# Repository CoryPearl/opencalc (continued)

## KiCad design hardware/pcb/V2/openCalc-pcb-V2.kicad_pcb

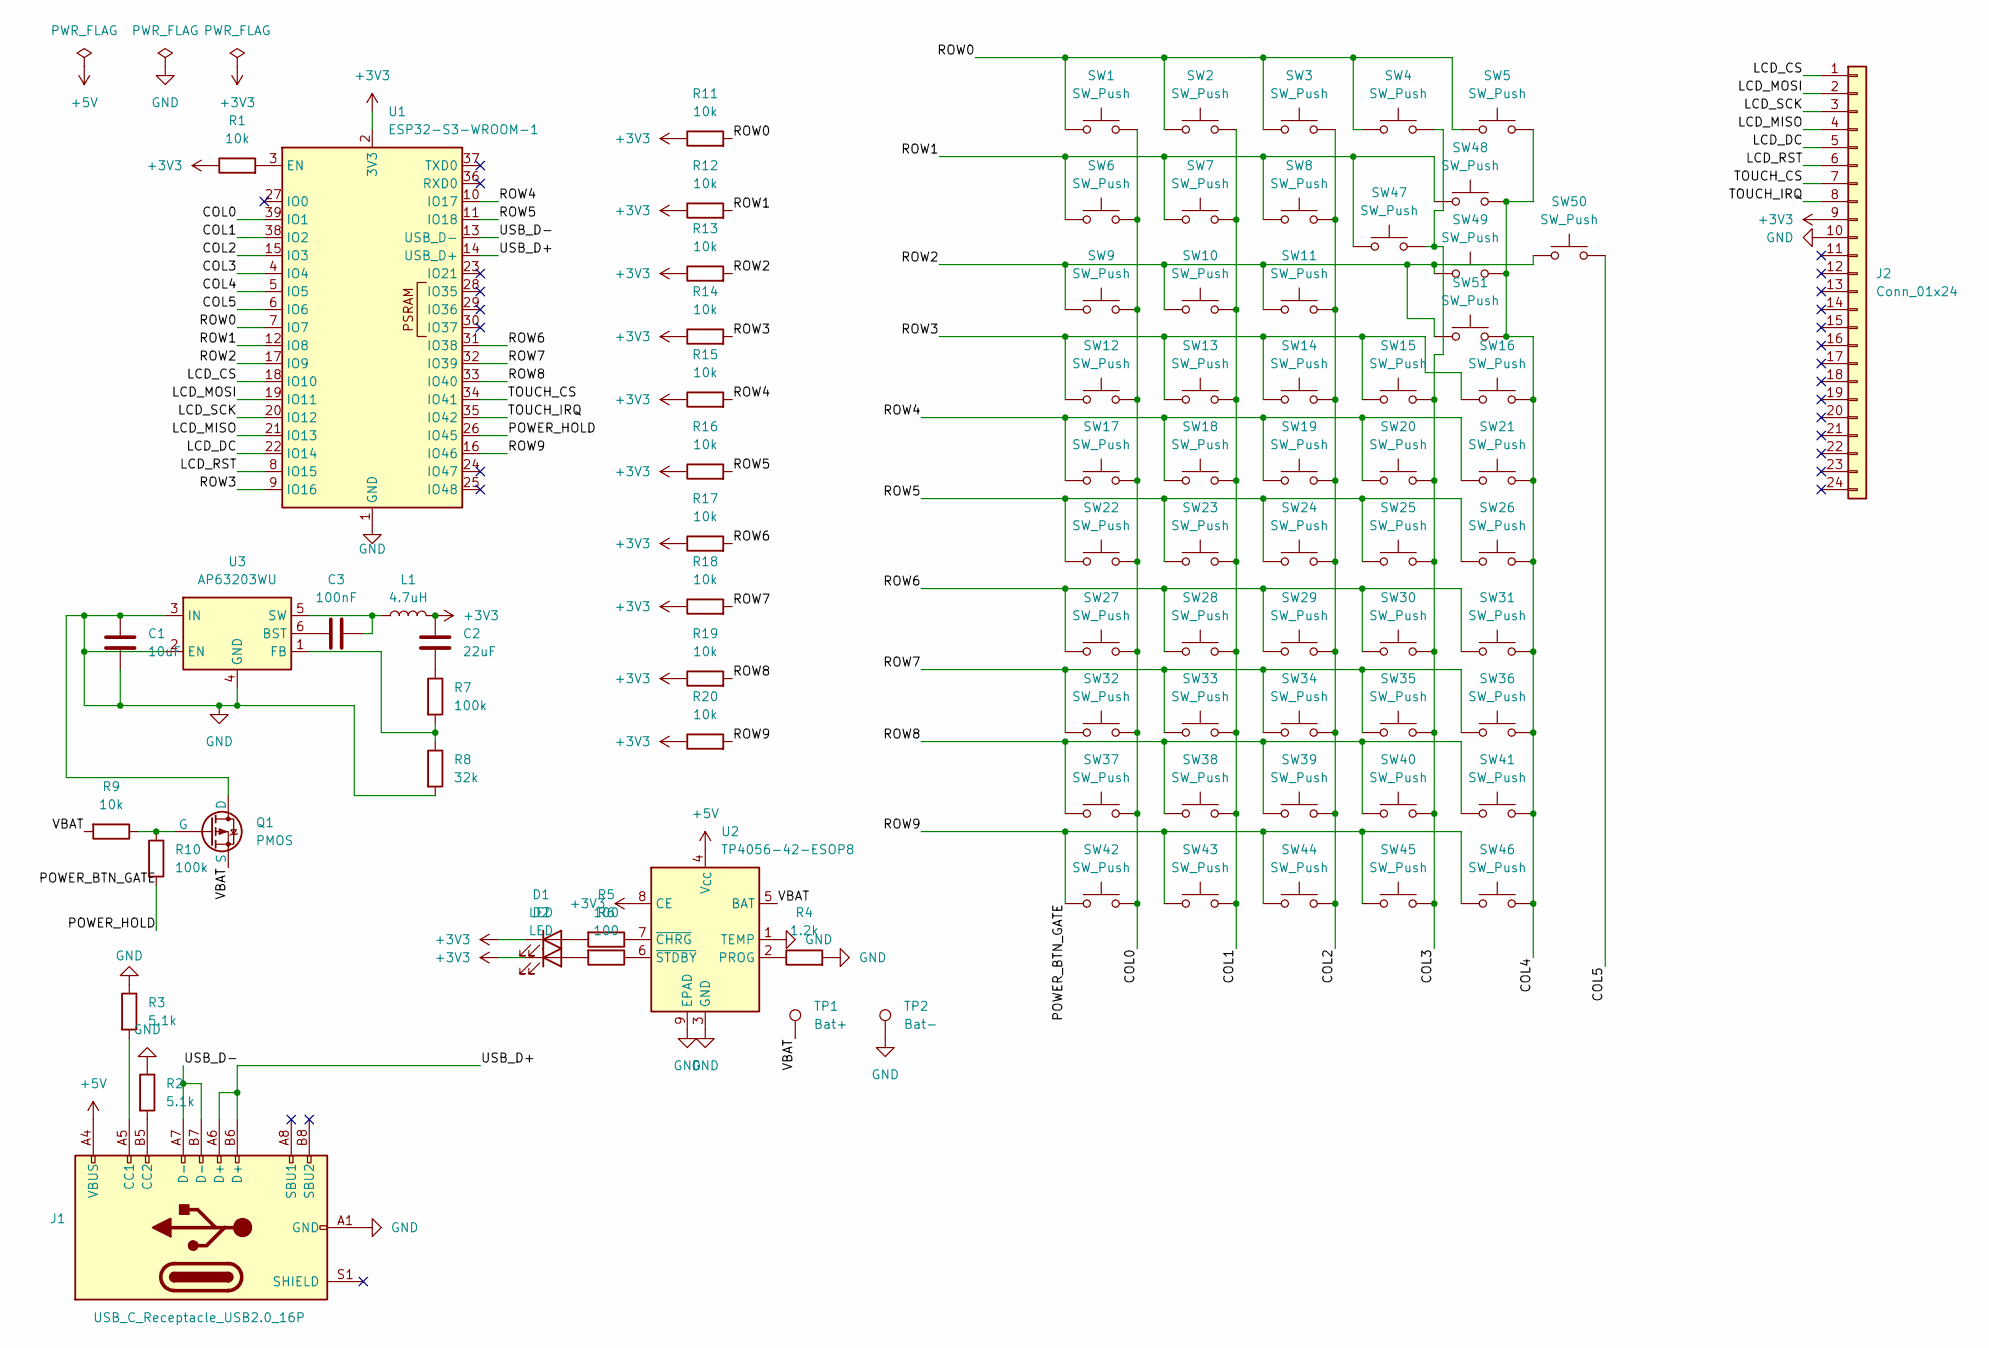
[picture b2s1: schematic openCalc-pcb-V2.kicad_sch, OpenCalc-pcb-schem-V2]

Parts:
C1: 10uF; C_0805_2012Metric
C2: 22uF; C_0805_2012Metric
C3: 100nF; C_0402_1005Metric
D1, D2: LED; LED_0402_1005Metric
J1: USB_C_Receptacle_USB2.0_16P; USB_C_Receptacle_GCT_USB4085
J2: Conn_01x24; PinHeader_1x24_P2.54mm_Vertical
L1: 4.7uH; L_0603_1608Metric
Q1: PMOS; SOT-23
R1, R9, R11, R12, R13, R14, R15, R16, R17, R18, R19, R20: 10k; R_0402_1005Metric
R2, R3: 5.1k; R_0402_1005Metric
R4: 1.2k; R_0402_1005Metric
R5, R6: 100; R_0402_1005Metric
R7, R10: 100k; R_0402_1005Metric
R8: 32k; R_0402_1005Metric
SW1, SW2, SW3, SW4, SW5, SW6, SW7, SW8, SW9, SW10, SW11, SW12, SW13, SW14, SW15, SW16, SW17, SW18, SW19, SW20, SW21, SW22, SW23, SW24, SW25, SW26, SW27, SW28, SW29, SW30, SW31, SW32, SW33, SW34, SW35, SW36, SW37, SW38, SW39, SW40, SW41, SW42, SW43, SW44, SW45, SW46, SW47, SW48, SW49, SW50, SW51: SW_Push; SW_PUSH_6mm
TP1: Bat+; TestPoint_Pad_D2.0mm
TP2: Bat-; TestPoint_Pad_D2.0mm
U1: ESP32-S3-WROOM-1
U2: TP4056-42-ESOP8; SOIC-8-1EP_3.9x4.9mm_P1.27mm_EP2.41x3.3mm_ThermalVias
U3: AP63203WU; TSOT-23-6

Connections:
+3V3: C2.1, D1.1 (K), D2.1 (K), J2.9, L1.2, R1.1, R11.1, R12.1, R13.1, R14.1, R15.1, R16.1, R17.1, R18.1, R19.1, R20.1, U1.2 (3V3), U2.8 (CE)
+5V: J1.A4 (VBUS), J1.A9 (VBUS), J1.B4 (VBUS), J1.B9 (VBUS), U2.4 (V_{CC})
/COL0: SW1.2, SW6.2, SW9.2, SW12.2, SW17.2, SW22.2, SW27.2, SW32.2, SW37.2, SW42.2, U1.39 (IO1)
/COL1: SW2.2, SW7.2, SW10.2, SW13.2, SW18.2, SW23.2, SW28.2, SW33.2, SW38.2, SW43.2, U1.38 (IO2)
/COL2: SW3.2, SW8.2, SW11.2, SW14.2, SW19.2, SW24.2, SW29.2, SW34.2, SW39.2, SW44.2, U1.15 (IO3)
/COL3: SW4.2, SW15.2, SW20.2, SW25.2, SW30.2, SW35.2, SW40.2, SW45.2, SW47.2, U1.4 (IO4)
/COL4: SW5.2, SW16.2, SW21.2, SW26.2, SW31.2, SW36.2, SW41.2, SW46.2, SW48.2, SW49.2, SW51.2, U1.5 (IO5)
/COL5: SW50.2, U1.6 (IO6)
/LCD_CS: J2.1, U1.18 (IO10)
/LCD_DC: J2.5, U1.22 (IO14)
/LCD_MISO: J2.4, U1.21 (IO13)
/LCD_MOSI: J2.2, U1.19 (IO11)
/LCD_RST: J2.6, U1.8 (IO15)
/LCD_SCK: J2.3, U1.20 (IO12)
/POWER_BTN_GATE: R10.2, R20.2, SW42.1, SW43.1, SW44.1, SW45.1, SW46.1, U1.16 (IO46), U1.26 (IO45)
/ROW0: R11.2, SW1.1, SW2.1, SW3.1, SW4.1, SW5.1, U1.7 (IO7)
/ROW1: R12.2, SW6.1, SW7.1, SW8.1, SW47.1, SW48.1, U1.12 (IO8)
/ROW2: R13.2, SW9.1, SW10.1, SW11.1, SW49.1, SW50.1, SW51.1, U1.17 (IO9)
/ROW3: R14.2, SW12.1, SW13.1, SW14.1, SW15.1, SW16.1, U1.9 (IO16)
/ROW4: R15.2, SW17.1, SW18.1, SW19.1, SW20.1, SW21.1, U1.10 (IO17)
/ROW5: R16.2, SW22.1, SW23.1, SW24.1, SW25.1, SW26.1, U1.11 (IO18)
/ROW6: R17.2, SW27.1, SW28.1, SW29.1, SW30.1, SW31.1, U1.31 (IO38)
/ROW7: R18.2, SW32.1, SW33.1, SW34.1, SW35.1, SW36.1, U1.32 (IO39)
/ROW8: R19.2, SW37.1, SW38.1, SW39.1, SW40.1, SW41.1, U1.33 (IO40)
/TOUCH_CS: J2.7, U1.34 (IO41)
/TOUCH_IRQ: J2.8, U1.35 (IO42)
/USB_D+: J1.A6 (D+), J1.B6 (D+), U1.14 (USB_D+)
/USB_D-: J1.A7 (D-), J1.B7 (D-), U1.13 (USB_D-)
/VBAT: Q1.3 (S), R9.2, TP1.1, U2.5 (BAT)
GND: C1.1, C1.2, J1.A1 (GND), J1.A12 (GND), J1.B1 (GND), J1.B12 (GND), J2.10, Q1.1 (D), R2.1, R3.1, R4.2, R8.2, TP2.1, U1.1 (GND), U1.40 (GND), U1.41 (GND), U2.1 (TEMP), U2.3 (GND), U2.9 (EPAD), U3.2 (EN), U3.3 (IN), U3.4 (GND)
unnamed: C2.2, R7.1
unnamed: D1.2 (A), R5.2
unnamed: D2.2 (A), R6.2
unnamed: J1.A5 (CC1), R3.2
unnamed: J1.B5 (CC2), R2.2
unnamed: Q1.2 (G), R9.1, R10.1
unnamed: R1.2, U1.3 (EN)
unnamed: R4.1, U2.2 (PROG)
unnamed: R5.1, U2.7 (~CHRG)
unnamed: R6.1, U2.6 (~STDBY)
unnamed: C3.1, U3.6 (BST)
unnamed: R7.2, R8.1, U3.1 (FB)
unnamed: C3.2, L1.1, U3.5 (SW)

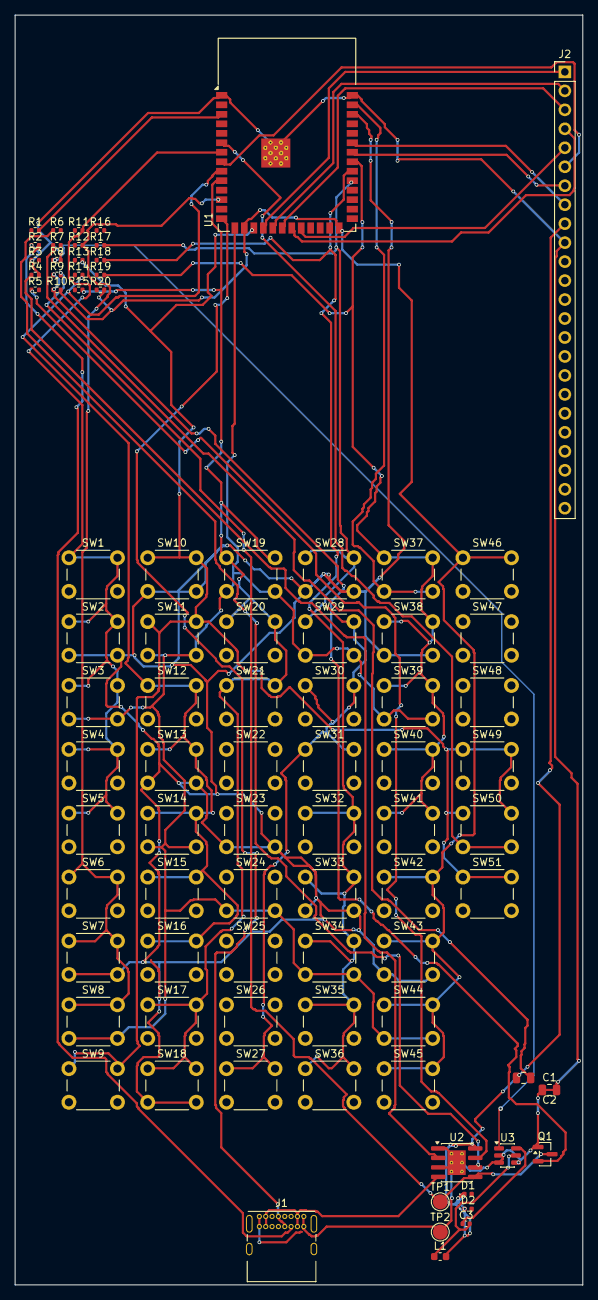
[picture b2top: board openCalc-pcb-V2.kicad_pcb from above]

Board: 2 copper layers, 76.0 x 170.0 mm, 85 parts (0 on the bottom side), 43 nets.

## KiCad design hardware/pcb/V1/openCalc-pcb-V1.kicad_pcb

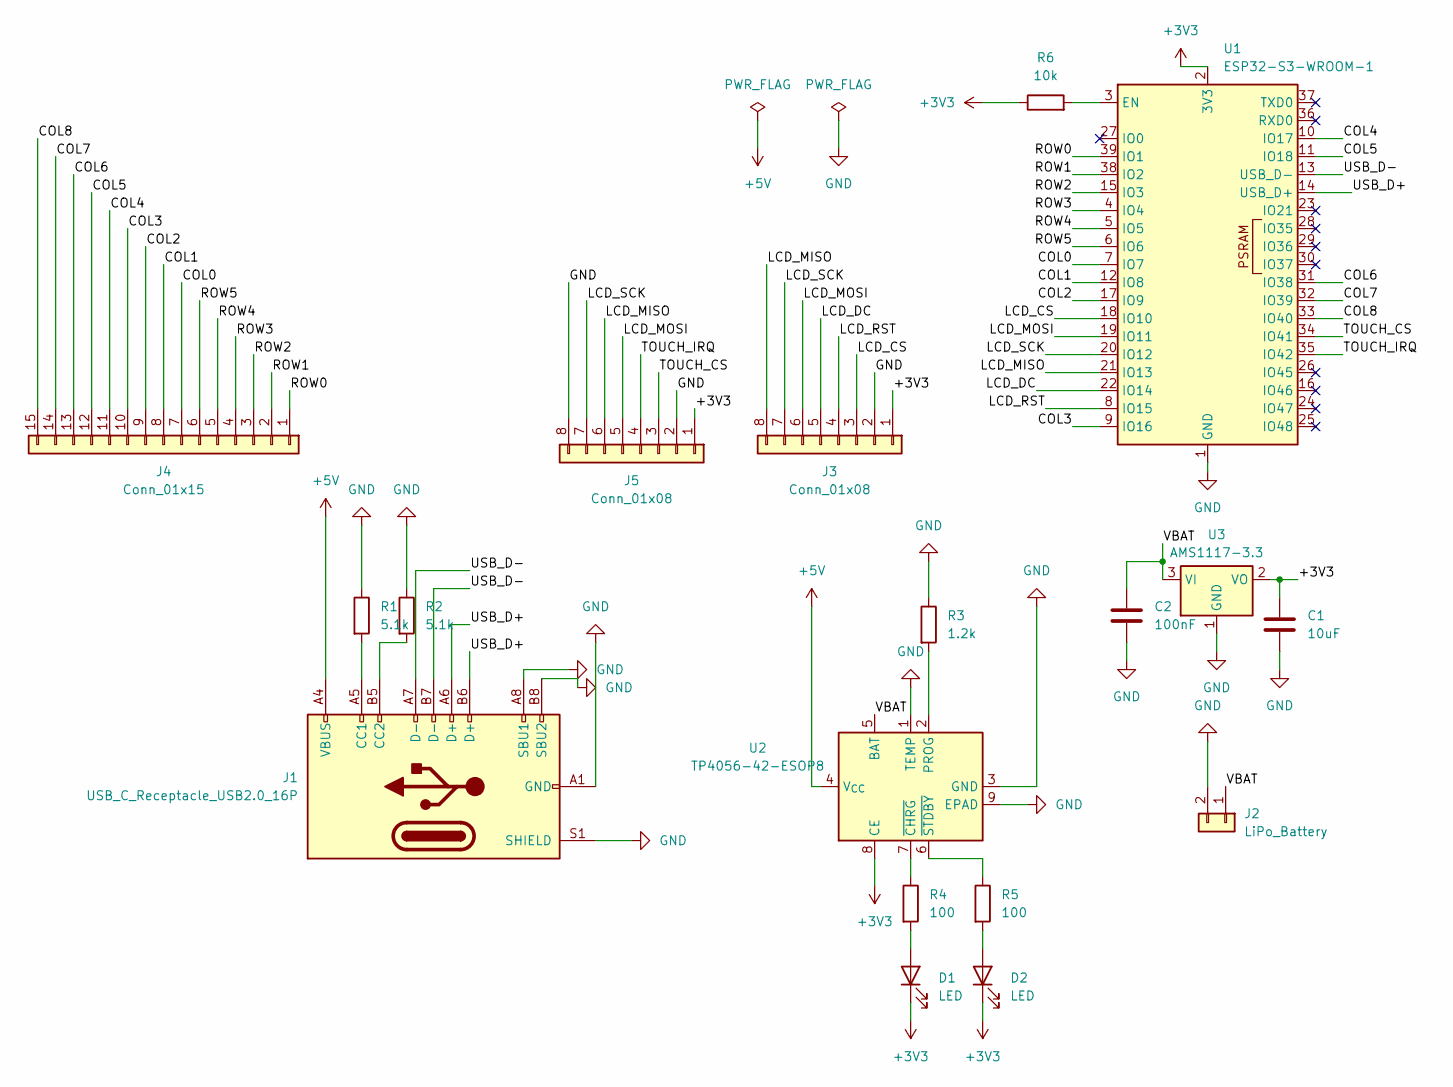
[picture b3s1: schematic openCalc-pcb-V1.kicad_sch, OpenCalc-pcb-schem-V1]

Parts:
C1: 10uF; C_0402_1005Metric
C2: 100nF; C_0402_1005Metric
D1, D2: LED; LED_0402_1005Metric
J1: USB_C_Receptacle_USB2.0_16P; USB_C_Receptacle_GCT_USB4085
J2: LiPo_Battery; PinHeader_1x02_P2.54mm_Vertical
J3, J5: Conn_01x08; PinHeader_1x08_P2.54mm_Vertical
J4: Conn_01x15; PinHeader_1x15_P2.54mm_Vertical
R1, R2: 5.1k; R_0402_1005Metric
R3: 1.2k; R_0402_1005Metric
R4, R5: 100; R_0402_1005Metric
R6: 10k; R_0402_1005Metric
U1: ESP32-S3-WROOM-1
U2: TP4056-42-ESOP8; SOIC-8-1EP_3.9x4.9mm_P1.27mm_EP2.41x3.3mm_ThermalVias
U3: AMS1117-3.3; SOT-223-3_TabPin2

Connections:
+3V3: C1.1, D1.1 (K), D2.1 (K), J3.1, J5.1, R6.1, U1.2 (3V3), U2.8 (CE), U3.2 (VO)
+5V: J1.A4 (VBUS), J1.A9 (VBUS), J1.B4 (VBUS), J1.B9 (VBUS), U2.4 (V_{CC})
/COL0: J4.7, U1.7 (IO7)
/COL1: J4.8, U1.12 (IO8)
/COL2: J4.9, U1.17 (IO9)
/COL3: J4.10, U1.9 (IO16)
/COL4: J4.11, U1.10 (IO17)
/COL5: J4.12, U1.11 (IO18)
/COL6: J4.13, U1.31 (IO38)
/COL7: J4.14, U1.32 (IO39)
/COL8: J4.15, U1.33 (IO40)
/LCD_CS: J3.3, U1.18 (IO10)
/LCD_DC: J3.5, U1.22 (IO14)
/LCD_MISO: J3.8, J5.6, U1.21 (IO13)
/LCD_MOSI: J3.6, J5.5, U1.19 (IO11)
/LCD_RST: J3.4, U1.8 (IO15)
/LCD_SCK: J3.7, J5.7, U1.20 (IO12)
/ROW0: J4.1, U1.39 (IO1)
/ROW1: J4.2, U1.38 (IO2)
/ROW2: J4.3, U1.15 (IO3)
/ROW3: J4.4, U1.4 (IO4)
/ROW4: J4.5, U1.5 (IO5)
/ROW5: J4.6, U1.6 (IO6)
/TOUCH_CS: J5.3, U1.34 (IO41)
/TOUCH_IRQ: J5.4, U1.35 (IO42)
/USB_D+: J1.A6 (D+), J1.B6 (D+), U1.14 (USB_D+)
/USB_D-: J1.A7 (D-), J1.B7 (D-), U1.13 (USB_D-)
/VBAT: C2.1, J2.1, U2.5 (BAT), U3.3 (VI)
GND: C1.2, C2.2, J1.A1 (GND), J1.A8 (SBU1), J1.A12 (GND), J1.B1 (GND), J1.B8 (SBU2), J1.B12 (GND), J1.S1 (SHIELD), J2.2, J3.2, J5.2, J5.8, R1.1, R2.1, R3.1, U1.1 (GND), U1.40 (GND), U1.41 (GND), U2.1 (TEMP), U2.3 (GND), U2.9 (EPAD), U3.1 (GND)
unnamed: D1.2 (A), R4.2
unnamed: D2.2 (A), R5.2
unnamed: J1.A5 (CC1), R1.2
unnamed: J1.B5 (CC2), R2.2
unnamed: R6.2, U1.3 (EN)
unnamed: R3.2, U2.2 (PROG)
unnamed: R4.1, U2.7 (~CHRG)
unnamed: R5.1, U2.6 (~STDBY)

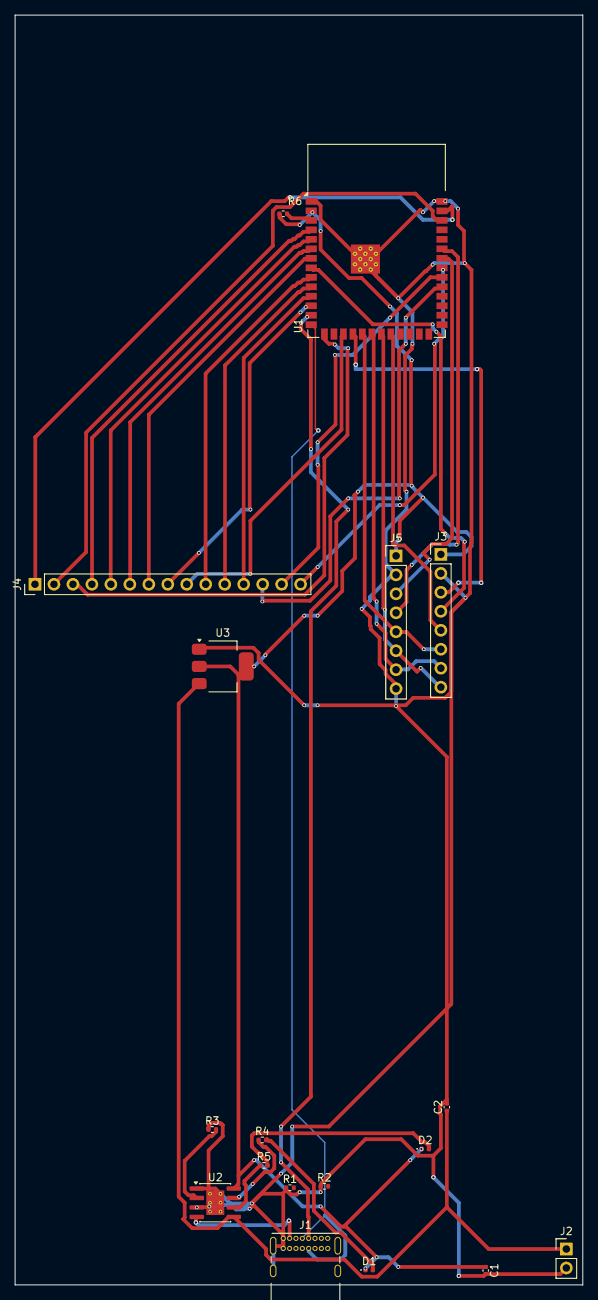
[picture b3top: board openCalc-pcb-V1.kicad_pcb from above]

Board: 2 copper layers, 76.0 x 170.0 mm, 18 parts (0 on the bottom side), 37 nets.

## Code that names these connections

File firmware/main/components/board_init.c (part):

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// OpenCalc PCB wiring.
//
// ESP32-S3 module nets:
//   ROW0..ROW9          -> GPIO1,2,42,4,5,6,48,8,9,16, pulled up to 3V3
//   COL0..COL4          -> GPIO17,18,38,39,40, driven by keypad scanner
//   USB_DM / USB_DP     -> GPIO19 / GPIO20
//   UART_TX / UART_RX   -> TXD0 / RXD0
//   VBAT_DIV            -> GPIO7 / ADC1 channel 6
//   CHG_STAT            -> Old PCB: GPIO41; removed from new audio PCB
//   GAME_AUDIO_PDM      -> New audio PCB: GPIO41, filtered PDM audio output
//   SENSOR_I2C_SDA/SCL  -> Scientific-I/O PCB: GPIO13/GPIO21
//   GAME_AUDIO_SD       -> Scientific-I/O PCB: MCP23017 GPA0
//   LCD_BACKL           -> GPIO47, backlight polarity selected in config.h
//   POWER_STATUS_LED    -> Scientific-I/O PCB: MCP23017 GPA1
//
// LCD touch is not wired on this PCB revision, so ENABLE_TOUCH_INPUT is 0.
//
//   VCC                  -> 3V3
//   GND                  -> GND
//   LCD_CS               -> GPIO10
//   LCD_RST              -> GPIO15
//   LCD_DC / RS          -> GPIO14
//   LCD_SDI / LCD_MOSI   -> GPIO11
//   LCD_SCK / LCD_SCLK   -> GPIO12
//   LCD_LED / backlight  -> Old PCB: TPS22918 output through 33 ohm.
//                            New PCB: AO3401A drain through 33 ohm; source is
//                            3V3 and gate is driven by GPIO47 through 100 ohm
//                            with a 100k pull-up to 3V3.
//                            Do not feed the LCD LED pin with 5V.
//   LCD_SDO / LCD_MISO   -> Old PCB: GPIO13; new audio PCB: unwired/write-only
//   Touch pins           -> unwired
#ifndef OPENCALC_HARDWARE_PROFILE_DEV_BOARD
#define OPENCALC_HARDWARE_PROFILE_DEV_BOARD 0
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
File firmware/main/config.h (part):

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/*
 * Scientific sensor header.
 *
 * The former AUDIO_SD/PWR_LED ESP pins, GPIO13/21, host a 400 kHz I2C bus
 * shared by the MCP23017 (0x20), ADS1115 (0x48), and external I2C sensors.
 * MCP23017 outputs return AUDIO_SD and PWR_LED control to those circuits.
 * The N16R8 module consumes GPIO35..37 for octal memory, while GPIO46 is an
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/*
 * Battery monitor.
 *
 * VBAT_DIV is a resistor divider into GPIO7 / ADC1 channel 6. The current PCB
 * uses 1M over 1M to reduce sleep drain. Keep the 100nF capacitor on the ADC
 * node so the high-value divider can settle before ADC reads.
 */
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
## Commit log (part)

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2026-05-29 thank the lord
2026-05-29 Added all build files and more scripting support to script better
